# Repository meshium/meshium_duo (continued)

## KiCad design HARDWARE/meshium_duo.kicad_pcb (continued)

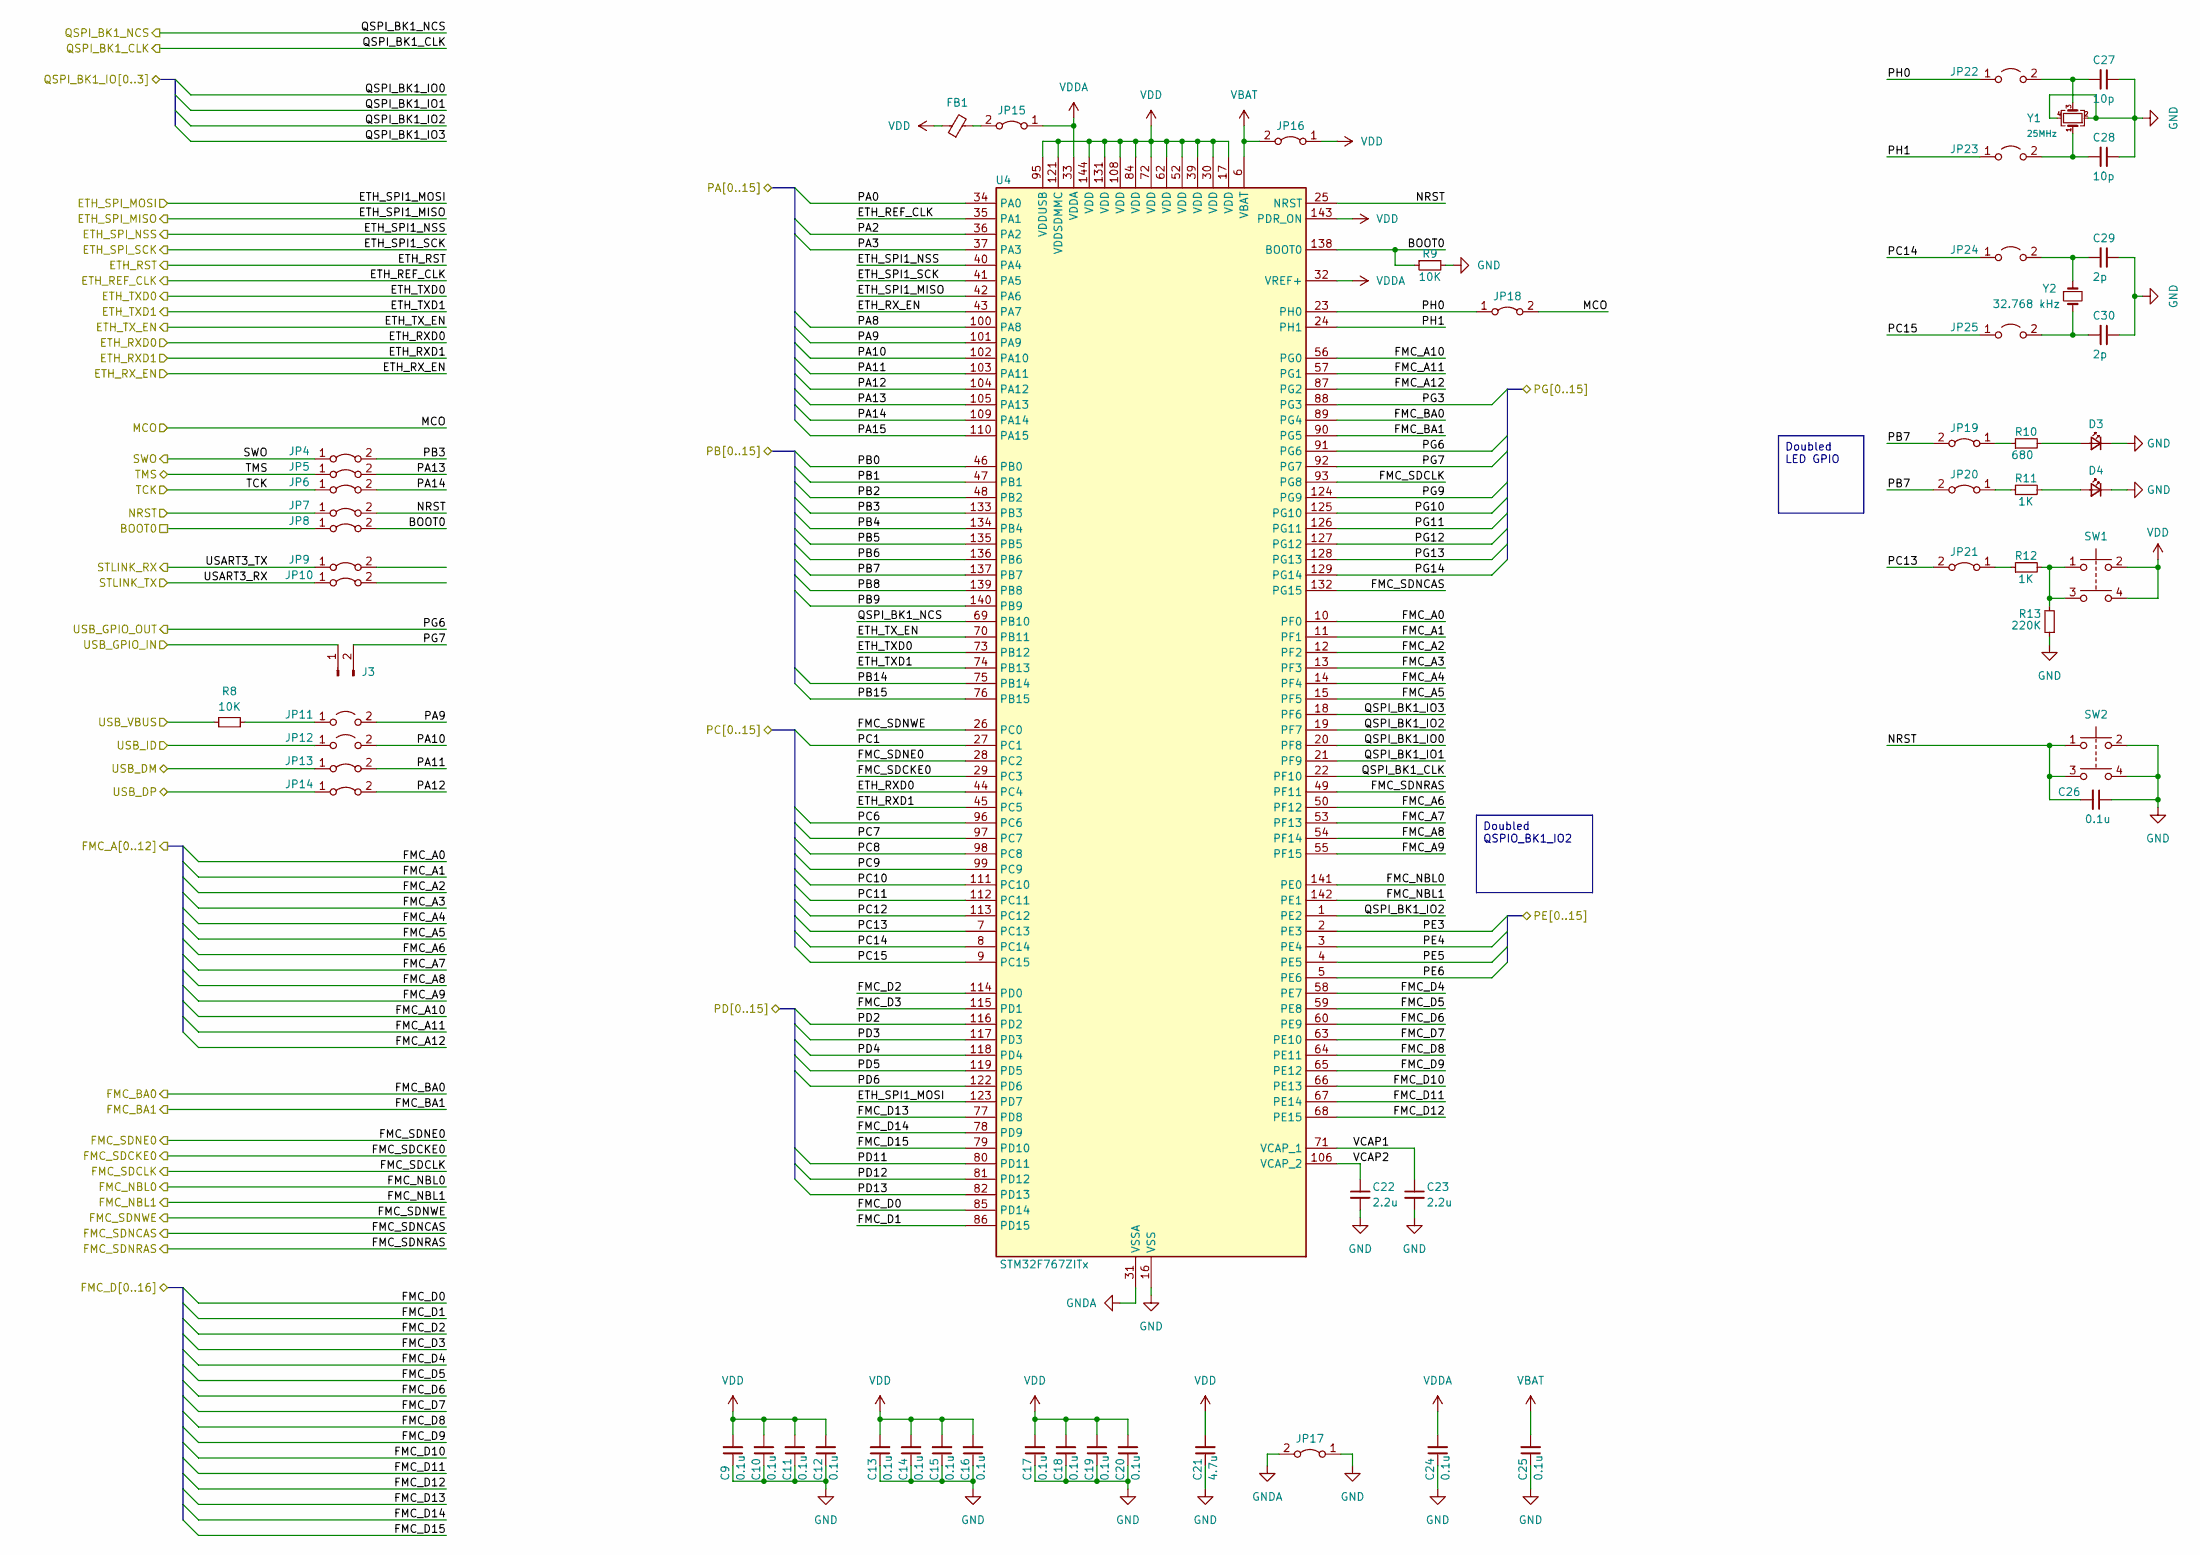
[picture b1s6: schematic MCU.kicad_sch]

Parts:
C9, C10, C11, C12, C13, C14, C15, C16, C17, C18, C19, C20, C24, C25, C26: 0.1u; C_0603_1608Metric
C21: 4.7u; C_0603_1608Metric
C22, C23: 2.2u; C_0805_2012Metric
C27, C28: 10p; C_0603_1608Metric
C29, C30: 2p; C_0603_1608Metric
D3, D4: LED_Small; LED_0603_1608Metric
FB1: FerriteBead_Small; C_0603_1608Metric
J3: Conn_01x02_Pin; PinHeader_1x02_P2.54mm_Vertical
JP4, JP5, JP6, JP7, JP8, JP9, JP10, JP13, JP14, JP15, JP16, JP17, JP18, JP19, JP20, JP21: Jumper_2_Bridged; SolderJumper-2_P1.3mm_Open_TrianglePad1.0x1.5mm
JP11, JP12, JP22, JP23, JP24, JP25: Jumper_2_Open; SolderJumper-2_P1.3mm_Open_TrianglePad1.0x1.5mm
R8, R9: 10K; R_0603_1608Metric
R10: 680; R_0603_1608Metric
R11, R12: 1K; R_0603_1608Metric
R13: 220K; R_0603_1608Metric
SW1, SW2: SW_Push_Dual
U4: STM32F767ZITx; LQFP-144_20x20mm_P0.5mm
Y1: 25MHz; Crystal_SMD_3225-4Pin_3.2x2.5mm
Y2: 32.768 kHz; Crystal_SMD_3215-2Pin_3.2x1.5mm

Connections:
/Connectors/BOOT0: JP8.1 (A), JP8.2 (B), R9.1, U4.138 (BOOT0); also elsewhere on the board
/Connectors/NRST: C26.2, JP7.1 (A), JP7.2 (B), SW2.1, SW2.3, U4.25 (NRST); also elsewhere on the board
/Connectors/PA0: U4.34 (PA0); also elsewhere on the board
/Connectors/PA2: U4.36 (PA2); also elsewhere on the board
/Connectors/PA3: U4.37 (PA3); also elsewhere on the board
/Connectors/PA8: U4.100 (PA8); also elsewhere on the board
/Connectors/PA9: JP11.2 (B), U4.101 (PA9); also elsewhere on the board
/Connectors/PA10: JP12.2 (B), U4.102 (PA10); also elsewhere on the board
/Connectors/PA11: JP13.2 (B), U4.103 (PA11); also elsewhere on the board
/Connectors/PA12: JP14.2 (B), U4.104 (PA12); also elsewhere on the board
/Connectors/PA13: JP5.2 (B), U4.105 (PA13); also elsewhere on the board
/Connectors/PA14: JP6.2 (B), U4.109 (PA14); also elsewhere on the board
/Connectors/PA15: U4.110 (PA15); also elsewhere on the board
/Connectors/PB0: U4.46 (PB0); also elsewhere on the board
/Connectors/PB1: U4.47 (PB1); also elsewhere on the board
/Connectors/PB2: U4.48 (PB2); also elsewhere on the board
/Connectors/PB3: JP4.2 (B), U4.133 (PB3); also elsewhere on the board
/Connectors/PB4: U4.134 (PB4); also elsewhere on the board
/Connectors/PB5: U4.135 (PB5); also elsewhere on the board
/Connectors/PB6: U4.136 (PB6); also elsewhere on the board
/Connectors/PB7: JP19.2 (B), JP20.2 (B), U4.137 (PB7); also elsewhere on the board
/Connectors/PB8: U4.139 (PB8); also elsewhere on the board
/Connectors/PB9: U4.140 (PB9); also elsewhere on the board
/Connectors/PB14: U4.75 (PB14); also elsewhere on the board
/Connectors/PB15: U4.76 (PB15); also elsewhere on the board
/Connectors/PC1: U4.27 (PC1); also elsewhere on the board
/Connectors/PC6: U4.96 (PC6); also elsewhere on the board
/Connectors/PC7: U4.97 (PC7); also elsewhere on the board
/Connectors/PC8: U4.98 (PC8); also elsewhere on the board
/Connectors/PC9: U4.99 (PC9); also elsewhere on the board
/Connectors/PC10: U4.111 (PC10); also elsewhere on the board
/Connectors/PC11: U4.112 (PC11); also elsewhere on the board
/Connectors/PC12: U4.113 (PC12); also elsewhere on the board
/Connectors/PC13: JP21.2 (B), U4.7 (PC13); also elsewhere on the board
/Connectors/PC14: JP24.1 (A), U4.8 (PC14); also elsewhere on the board
/Connectors/PC15: JP25.1 (A), U4.9 (PC15); also elsewhere on the board
/Connectors/PD2: U4.116 (PD2); also elsewhere on the board
/Connectors/PD3: U4.117 (PD3); also elsewhere on the board
/Connectors/PD4: U4.118 (PD4); also elsewhere on the board
/Connectors/PD5: U4.119 (PD5); also elsewhere on the board
/Connectors/PD6: U4.122 (PD6); also elsewhere on the board
/Connectors/PD11: U4.80 (PD11); also elsewhere on the board
/Connectors/PD12: U4.81 (PD12); also elsewhere on the board
/Connectors/PD13: U4.82 (PD13); also elsewhere on the board
/Connectors/PE3: U4.2 (PE3); also elsewhere on the board
/Connectors/PE4: U4.3 (PE4); also elsewhere on the board
/Connectors/PE5: U4.4 (PE5); also elsewhere on the board
/Connectors/PE6: U4.5 (PE6); also elsewhere on the board
/Connectors/PG3: U4.88 (PG3); also elsewhere on the board
/Connectors/PG6: U4.91 (PG6); also elsewhere on the board
/Connectors/PG7: J3.2, U4.92 (PG7); also elsewhere on the board
/Connectors/PG9: U4.124 (PG9); also elsewhere on the board
/Connectors/PG10: U4.125 (PG10); also elsewhere on the board
/Connectors/PG11: U4.126 (PG11); also elsewhere on the board
/Connectors/PG12: U4.127 (PG12); also elsewhere on the board
/Connectors/PG13: U4.128 (PG13); also elsewhere on the board
/Connectors/PG14: U4.129 (PG14); also elsewhere on the board
/Ethernet/ETH_REF_CLK: U4.35 (PA1); also elsewhere on the board
/Ethernet/ETH_RXD0: U4.44 (PC4); also elsewhere on the board
/Ethernet/ETH_RXD1: U4.45 (PC5); also elsewhere on the board
/Ethernet/ETH_RX_EN: U4.43 (PA7); also elsewhere on the board
/Ethernet/ETH_SPI_MISO: U4.42 (PA6); also elsewhere on the board
/Ethernet/ETH_SPI_MOSI: U4.123 (PD7); also elsewhere on the board
/Ethernet/ETH_SPI_NSS: U4.40 (PA4); also elsewhere on the board
/Ethernet/ETH_SPI_SCK: U4.41 (PA5); also elsewhere on the board
/Ethernet/ETH_TXD0: U4.73 (PB12); also elsewhere on the board
/Ethernet/ETH_TXD1: U4.74 (PB13); also elsewhere on the board
/Ethernet/ETH_TX_EN: U4.70 (PB11); also elsewhere on the board
/MCU/FMC_A0: U4.10 (PF0); also elsewhere on the board
/MCU/FMC_A1: U4.11 (PF1); also elsewhere on the board
/MCU/FMC_A2: U4.12 (PF2); also elsewhere on the board
/MCU/FMC_A3: U4.13 (PF3); also elsewhere on the board
/MCU/FMC_A4: U4.14 (PF4); also elsewhere on the board
/MCU/FMC_A5: U4.15 (PF5); also elsewhere on the board
/MCU/FMC_A6: U4.50 (PF12); also elsewhere on the board
/MCU/FMC_A7: U4.53 (PF13); also elsewhere on the board
/MCU/FMC_A8: U4.54 (PF14); also elsewhere on the board
/MCU/FMC_A9: U4.55 (PF15); also elsewhere on the board
/MCU/FMC_A10: U4.56 (PG0); also elsewhere on the board
/MCU/FMC_A11: U4.57 (PG1); also elsewhere on the board
/MCU/FMC_A12: U4.87 (PG2); also elsewhere on the board
/MCU/FMC_BA0: U4.89 (PG4); also elsewhere on the board
/MCU/FMC_BA1: U4.90 (PG5); also elsewhere on the board
/MCU/FMC_D0: U4.85 (PD14); also elsewhere on the board
/MCU/FMC_D1: U4.86 (PD15); also elsewhere on the board
/MCU/FMC_D2: U4.114 (PD0); also elsewhere on the board
/MCU/FMC_D3: U4.115 (PD1); also elsewhere on the board
/MCU/FMC_D4: U4.58 (PE7); also elsewhere on the board
/MCU/FMC_D5: U4.59 (PE8); also elsewhere on the board
/MCU/FMC_D6: U4.60 (PE9); also elsewhere on the board
/MCU/FMC_D7: U4.63 (PE10); also elsewhere on the board
/MCU/FMC_D8: U4.64 (PE11); also elsewhere on the board
/MCU/FMC_D9: U4.65 (PE12); also elsewhere on the board
/MCU/FMC_D10: U4.66 (PE13); also elsewhere on the board
/MCU/FMC_D11: U4.67 (PE14); also elsewhere on the board
/MCU/FMC_D12: U4.68 (PE15); also elsewhere on the board
/MCU/FMC_D13: U4.77 (PD8); also elsewhere on the board
/MCU/FMC_D14: U4.78 (PD9); also elsewhere on the board
/MCU/FMC_D15: U4.79 (PD10); also elsewhere on the board
/MCU/FMC_NBL0: U4.141 (PE0); also elsewhere on the board
/MCU/FMC_NBL1: U4.142 (PE1); also elsewhere on the board
/MCU/FMC_SDCKE0: U4.29 (PC3); also elsewhere on the board
/MCU/FMC_SDCLK: U4.93 (PG8); also elsewhere on the board
/MCU/FMC_SDNCAS: U4.132 (PG15); also elsewhere on the board
/MCU/FMC_SDNE0: U4.28 (PC2); also elsewhere on the board
/MCU/FMC_SDNRAS: U4.49 (PF11); also elsewhere on the board
/MCU/FMC_SDNWE: U4.26 (PC0); also elsewhere on the board
/MCU/MCO: JP18.2 (B); also elsewhere on the board
/MCU/PH0: JP18.1 (A), JP22.1 (A), U4.23 (PH0)
/MCU/PH1: JP23.1 (A), U4.24 (PH1)
/MCU/QSPI_BK1_CLK: U4.22 (PF10); also elsewhere on the board
/MCU/QSPI_BK1_IO0: U4.20 (PF8); also elsewhere on the board
/MCU/QSPI_BK1_IO1: U4.21 (PF9); also elsewhere on the board
/MCU/QSPI_BK1_IO2: U4.1 (PE2), U4.19 (PF7); also elsewhere on the board
/MCU/QSPI_BK1_IO3: U4.18 (PF6); also elsewhere on the board
/MCU/QSPI_BK1_NCS: U4.69 (PB10); also elsewhere on the board
/MCU/SWO: JP4.1 (A); also elsewhere on the board
/MCU/TCK: JP6.1 (A); also elsewhere on the board
/MCU/TMS: JP5.1 (A); also elsewhere on the board
/MCU/USART3_RX: JP10.1 (A); also elsewhere on the board
/MCU/USART3_TX: JP9.1 (A); also elsewhere on the board
/MCU/USB_DM: JP13.1 (A); also elsewhere on the board
/MCU/USB_DP: JP14.1 (A); also elsewhere on the board
/MCU/USB_GPIO_IN: J3.1; also elsewhere on the board
/MCU/USB_ID: JP12.1 (A); also elsewhere on the board
/MCU/USB_VBUS: R8.1; also elsewhere on the board
GNDA: JP17.2 (B), U4.31 (VSSA); also elsewhere on the board
unnamed: D3.2 (A), R10.2
unnamed: D4.2 (A), R11.2
unnamed: JP11.1 (A), R8.2
unnamed: FB1.2, JP15.2 (B)
unnamed: JP19.1 (A), R10.1
unnamed: JP20.1 (A), R11.1
unnamed: JP21.1 (A), R12.1
unnamed: C27.2, JP22.2 (B), Y1.3
unnamed: C28.2, JP23.2 (B), Y1.1
unnamed: C29.2, JP24.2 (B), Y2.1
unnamed: C30.2, JP25.2 (B), Y2.3
unnamed: R12.2, R13.2, SW1.1, SW1.3
unnamed: C23.1, U4.71 (VCAP_1)
unnamed: C22.1, U4.106 (VCAP_2)
VBAT: C25.2, JP16.2 (B), U4.6 (VBAT); also elsewhere on the board
VDD: C9.2, C10.2, C11.2, C12.2, C13.2, C14.2, C15.2, C16.2, C17.2, C18.2, C19.2, C20.2, C21.2, FB1.1, JP16.1 (A), SW1.2, SW1.4, U4.17 (VDD), U4.30 (VDD), U4.39 (VDD), U4.52 (VDD), U4.62 (VDD), U4.72 (VDD), U4.84 (VDD), U4.95 (VDDUSB), U4.108 (VDD), U4.121 (VDDSDMMC), U4.131 (VDD), U4.143 (PDR_ON), U4.144 (VDD); also elsewhere on the board
VDDA: C24.2, JP15.1 (A), U4.32 (VREF+), U4.33 (VDDA); also elsewhere on the board

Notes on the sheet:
Doubled QSPIO_BK1_IO2
Doubled LED GPIO

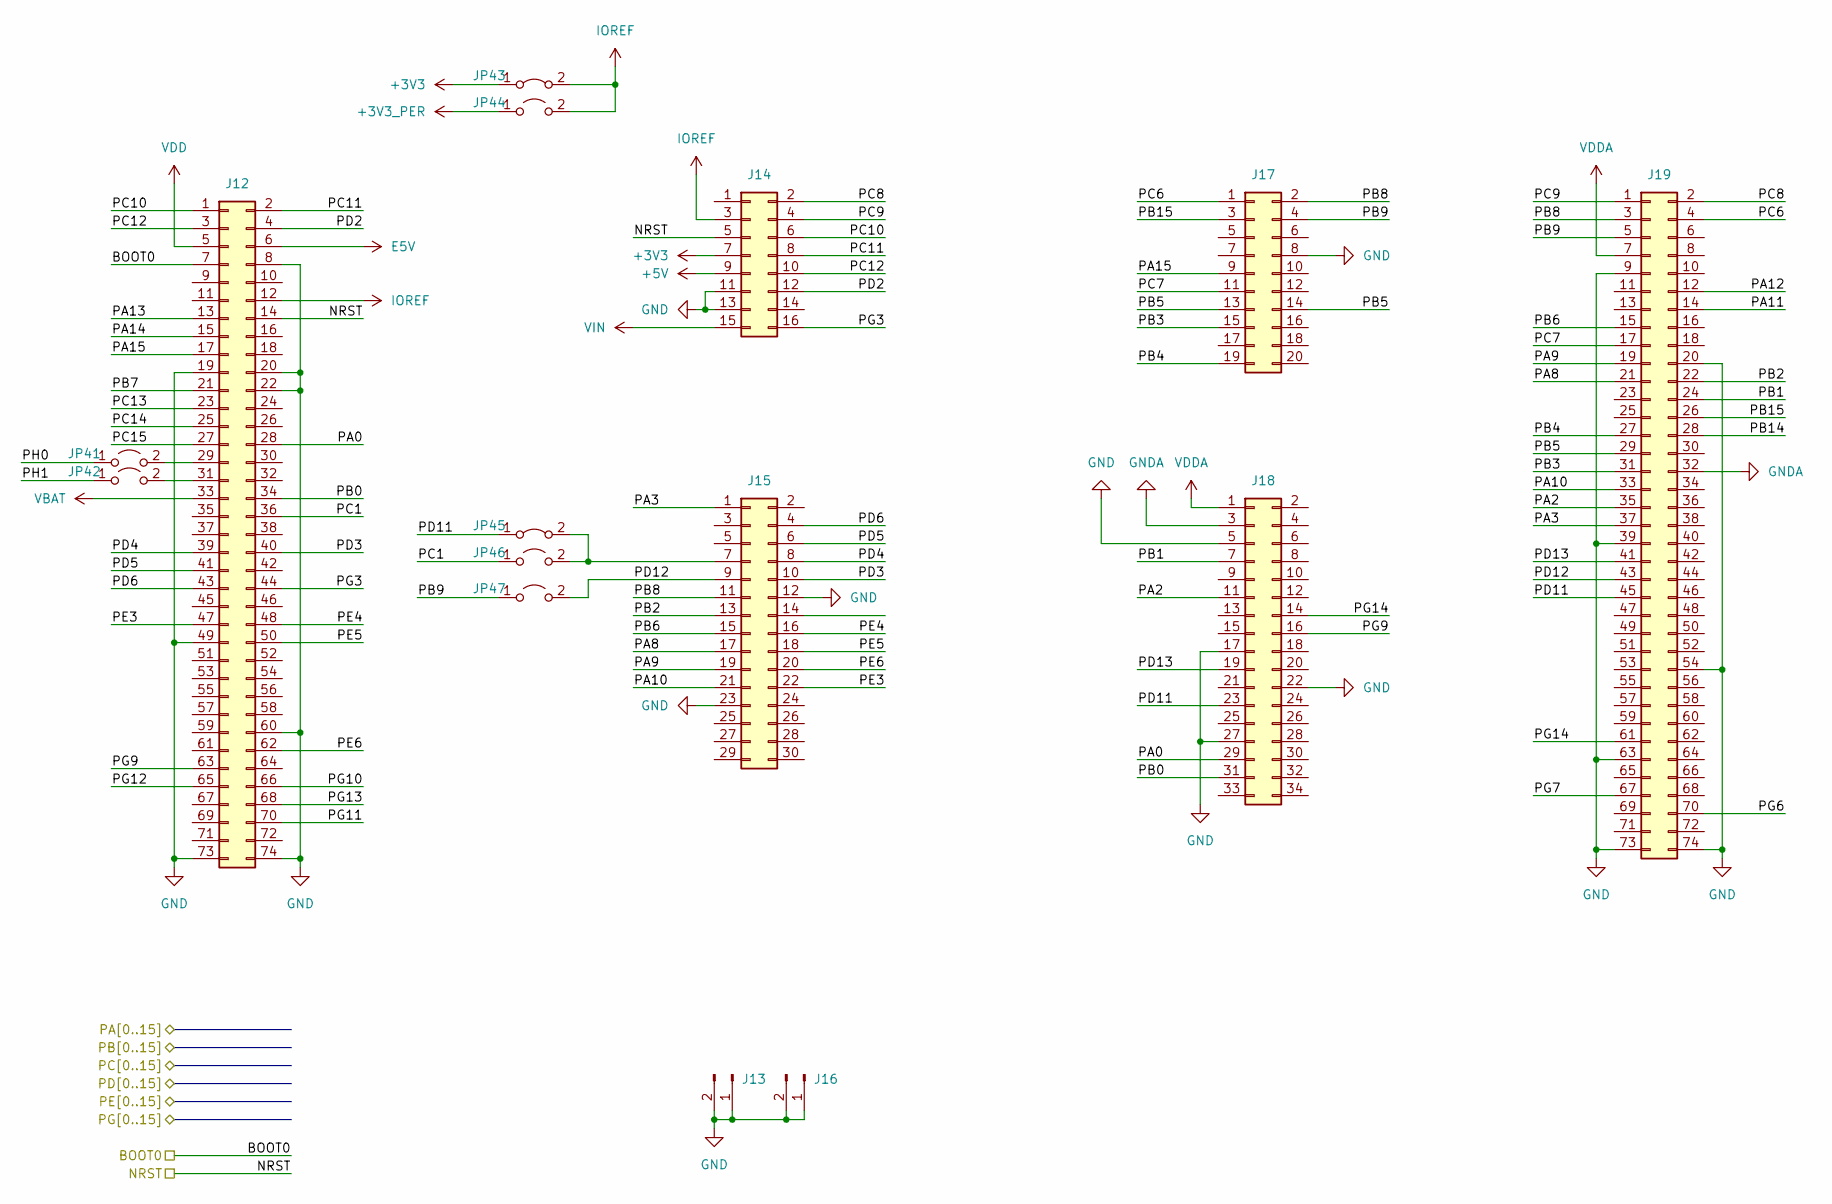
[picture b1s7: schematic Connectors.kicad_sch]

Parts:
J12, J19: Conn_02x37_Odd_Even; PinHeader_2x37_P2.54mm_Vertical
J13, J16: Conn_01x02_Pin; PinHeader_1x02_P2.54mm_Vertical
J14: Conn_02x08_Odd_Even; PinHeader_2x08_P2.54mm_Vertical
J15: Conn_02x15_Odd_Even; PinHeader_2x15_P2.54mm_Vertical
J17: Conn_02x10_Odd_Even; PinHeader_2x10_P2.54mm_Vertical
J18: Conn_02x17_Odd_Even; PinHeader_2x16_P2.54mm_Vertical
JP41, JP42, JP44, JP46, JP47: Jumper_2_Open; SolderJumper-2_P1.3mm_Open_TrianglePad1.0x1.5mm
JP43, JP45: Jumper_2_Bridged; SolderJumper-2_P1.3mm_Open_TrianglePad1.0x1.5mm

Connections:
+3V3_PER: JP44.1 (A); also elsewhere on the board
+5V: J14.9; also elsewhere on the board
/Connectors/BOOT0: J12.7; also elsewhere on the board
/Connectors/NRST: J12.14, J14.5; also elsewhere on the board
/Connectors/PA0: J12.28, J18.29; also elsewhere on the board
/Connectors/PA2: J18.11, J19.35; also elsewhere on the board
/Connectors/PA3: J15.1, J19.37; also elsewhere on the board
/Connectors/PA8: J15.17, J19.21; also elsewhere on the board
/Connectors/PA9: J15.19, J19.19; also elsewhere on the board
/Connectors/PA10: J15.21, J19.33; also elsewhere on the board
/Connectors/PA11: J19.14; also elsewhere on the board
/Connectors/PA12: J19.12; also elsewhere on the board
/Connectors/PA13: J12.13; also elsewhere on the board
/Connectors/PA14: J12.15; also elsewhere on the board
/Connectors/PA15: J12.17, J17.9; also elsewhere on the board
/Connectors/PB0: J12.34, J18.31; also elsewhere on the board
/Connectors/PB1: J18.7, J19.24; also elsewhere on the board
/Connectors/PB2: J15.13, J19.22; also elsewhere on the board
/Connectors/PB3: J17.15, J19.31; also elsewhere on the board
/Connectors/PB4: J17.19, J19.27; also elsewhere on the board
/Connectors/PB5: J17.13, J17.14, J19.29; also elsewhere on the board
/Connectors/PB6: J15.15, J19.15; also elsewhere on the board
/Connectors/PB7: J12.21; also elsewhere on the board
/Connectors/PB8: J15.11, J17.2, J19.3; also elsewhere on the board
/Connectors/PB9: J17.4, J19.5, JP47.1 (A); also elsewhere on the board
/Connectors/PB14: J19.28; also elsewhere on the board
/Connectors/PB15: J17.3, J19.26; also elsewhere on the board
/Connectors/PC1: J12.36, JP46.1 (A); also elsewhere on the board
/Connectors/PC6: J17.1, J19.4; also elsewhere on the board
/Connectors/PC7: J17.11, J19.17; also elsewhere on the board
/Connectors/PC8: J14.2, J19.2; also elsewhere on the board
/Connectors/PC9: J14.4, J19.1; also elsewhere on the board
/Connectors/PC10: J12.1, J14.6; also elsewhere on the board
/Connectors/PC11: J12.2, J14.8; also elsewhere on the board
/Connectors/PC12: J12.3, J14.10; also elsewhere on the board
/Connectors/PC13: J12.23; also elsewhere on the board
/Connectors/PC14: J12.25; also elsewhere on the board
/Connectors/PC15: J12.27; also elsewhere on the board
/Connectors/PD2: J12.4, J14.12; also elsewhere on the board
/Connectors/PD3: J12.40, J15.10; also elsewhere on the board
/Connectors/PD4: J12.39, J15.8; also elsewhere on the board
/Connectors/PD5: J12.41, J15.6; also elsewhere on the board
/Connectors/PD6: J12.43, J15.4; also elsewhere on the board
/Connectors/PD11: J18.23, J19.45, JP45.1 (A); also elsewhere on the board
/Connectors/PD12: J15.9, J19.43, JP47.2 (B); also elsewhere on the board
/Connectors/PD13: J18.19, J19.41; also elsewhere on the board
/Connectors/PE3: J12.47, J15.22; also elsewhere on the board
/Connectors/PE4: J12.48, J15.16; also elsewhere on the board
/Connectors/PE5: J12.50, J15.18; also elsewhere on the board
/Connectors/PE6: J12.62, J15.20; also elsewhere on the board
/Connectors/PG3: J12.44, J14.16; also elsewhere on the board
/Connectors/PG6: J19.70; also elsewhere on the board
/Connectors/PG7: J19.67; also elsewhere on the board
/Connectors/PG9: J12.63, J18.16; also elsewhere on the board
/Connectors/PG10: J12.66; also elsewhere on the board
/Connectors/PG11: J12.70; also elsewhere on the board
/Connectors/PG12: J12.65; also elsewhere on the board
/Connectors/PG13: J12.68; also elsewhere on the board
/Connectors/PG14: J18.14, J19.61; also elsewhere on the board
/Connectors/PH0: JP41.1 (A)
/Connectors/PH1: JP42.1 (A)
E5V: J12.6; also elsewhere on the board
GNDA: J18.3, J19.32; also elsewhere on the board
IOREF: J12.12, J14.3, JP43.2 (B), JP44.2 (B)
unnamed: J12.29, JP41.2 (B)
unnamed: J12.31, JP42.2 (B)
unnamed: J15.7, JP45.2 (B), JP46.2 (B)
VBAT: J12.33; also elsewhere on the board
VDD: J12.5; also elsewhere on the board
VDDA: J18.1, J19.7; also elsewhere on the board
VIN: J14.15; also elsewhere on the board

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
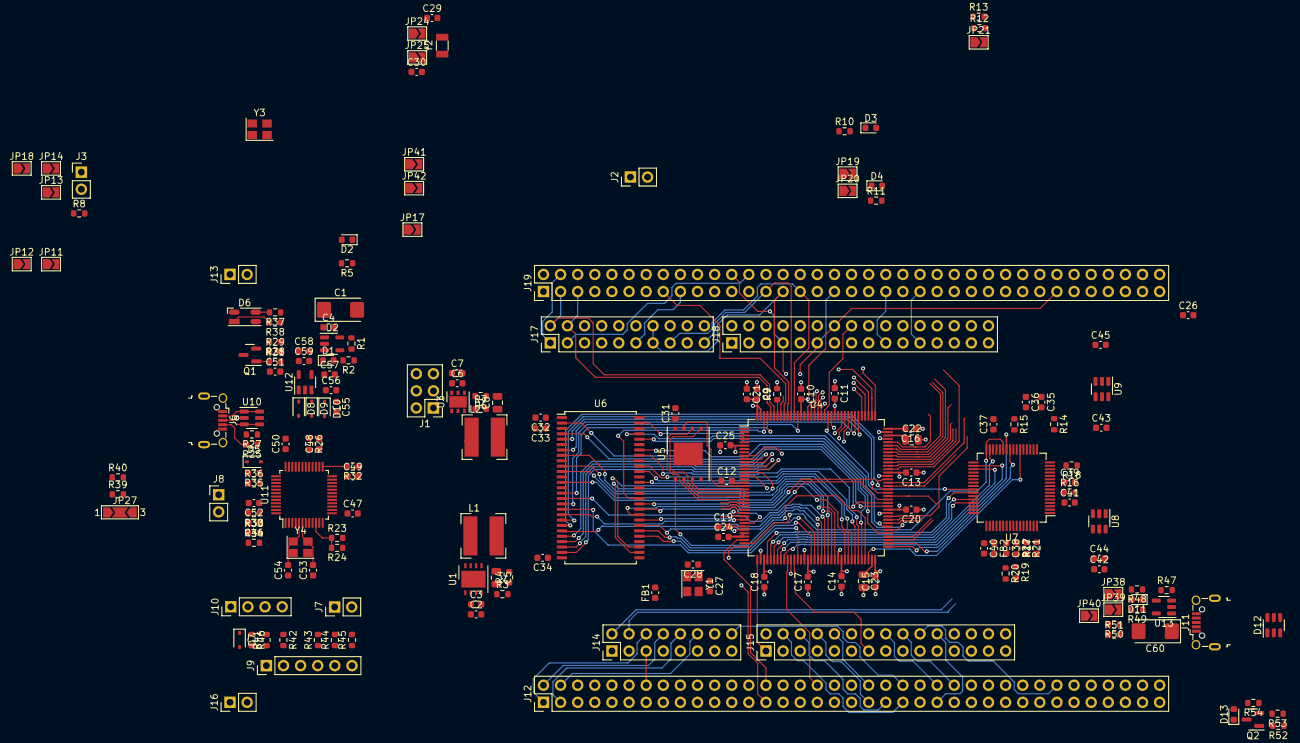
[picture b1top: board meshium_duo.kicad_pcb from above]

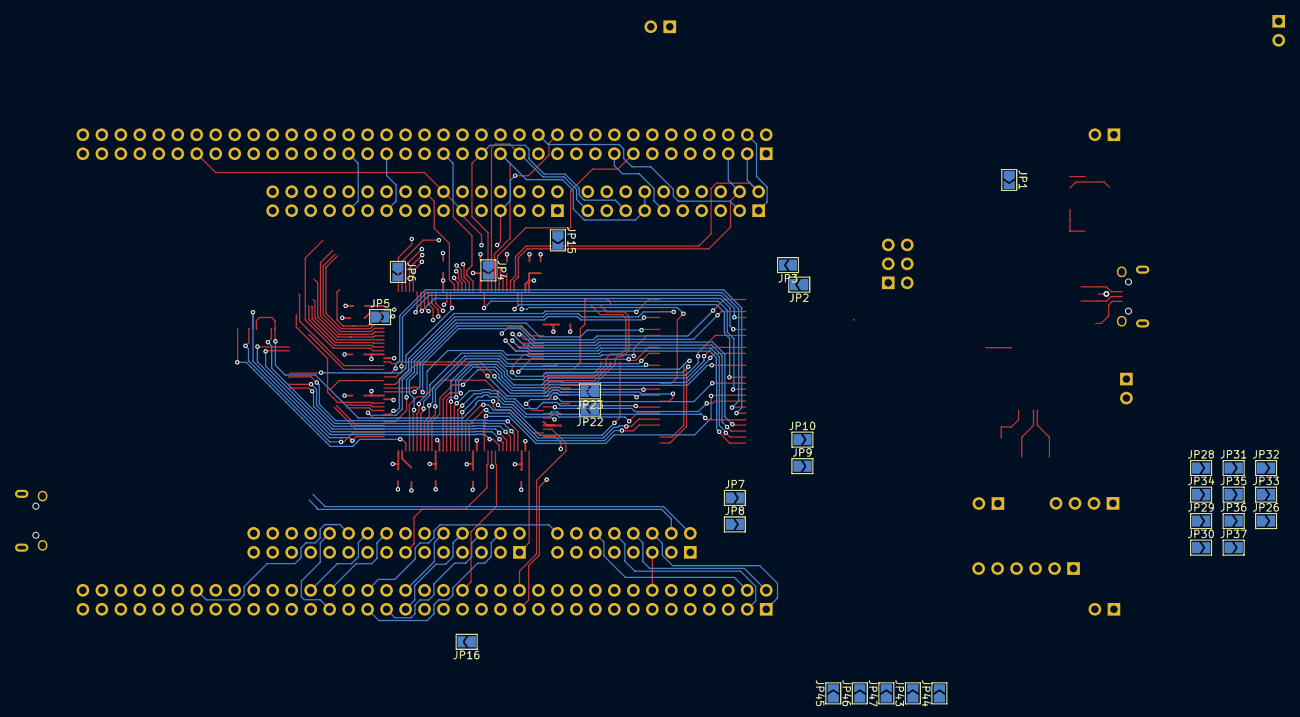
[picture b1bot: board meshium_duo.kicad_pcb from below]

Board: 6 copper layers, 214 parts (30 on the bottom side), 235 nets.

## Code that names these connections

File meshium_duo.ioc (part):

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Mcu.Name=STM32F767ZGTx
Mcu.Package=LQFP144
Mcu.UserName=STM32F767ZGTx
PA1.Mode=RMII
PA1.Signal=ETH_REF_CLK
PA2.Mode=RMII
PA2.Signal=ETH_MDIO
PA4.Mode=NSS_Signal_Hard_Output
PA4.Signal=SPI1_NSS
PA5.Mode=Full_Duplex_Master
PA5.Signal=SPI1_SCK
PA6.Mode=Full_Duplex_Master
PA6.Signal=SPI1_MISO
PA7.Mode=RMII
PA7.Signal=ETH_CRS_DV
PB10.Mode=Single Bank 1
PB10.Signal=QUADSPI_BK1_NCS
PB11.Mode=RMII
PB11.Signal=ETH_TX_EN
PB12.Mode=RMII
PB12.Signal=ETH_TXD0
PB13.Mode=RMII
PB13.Signal=ETH_TXD1
PC0.Signal=FMC_SDNWE
PC1.Mode=RMII
PC1.Signal=ETH_MDC
PC10.Mode=SD_4_bits_Wide_bus
PC10.Signal=SDMMC1_D2
PC11.Mode=SD_4_bits_Wide_bus
PC11.Signal=SDMMC1_D3
PC12.Mode=SD_4_bits_Wide_bus
PC12.Signal=SDMMC1_CK
PC2.Mode=SdramChipSelect1_1
PC2.Signal=FMC_SDNE0
PC3.Mode=SdramChipSelect1_1
PC3.Signal=FMC_SDCKE0
PC4.Mode=RMII
PC4.Signal=ETH_RXD0
PC5.Mode=RMII
PC5.Signal=ETH_RXD1
PC8.Mode=SD_4_bits_Wide_bus
PC8.Signal=SDMMC1_D0
PC9.Mode=SD_4_bits_Wide_bus
PC9.Signal=SDMMC1_D1
PD0.Signal=FMC_D2_DA2
PD1.Signal=FMC_D3_DA3
PD10.Signal=FMC_D15_DA15
PD14.Signal=FMC_D0_DA0
PD15.Signal=FMC_D1_DA1
PD2.Mode=SD_4_bits_Wide_bus
PD2.Signal=SDMMC1_CMD
PD7.Mode=Full_Duplex_Master
PD7.Signal=SPI1_MOSI
PD8.Signal=FMC_D13_DA13
PD9.Signal=FMC_D14_DA14
PE0.Signal=FMC_NBL0
PE1.Signal=FMC_NBL1
PE10.Signal=FMC_D7_DA7
PE11.Signal=FMC_D8_DA8
PE12.Signal=FMC_D9_DA9
PE13.Signal=FMC_D10_DA10
PE14.Signal=FMC_D11_DA11
PE15.Signal=FMC_D12_DA12
PE2.Mode=Single Bank 1
PE2.Signal=QUADSPI_BK1_IO2
PE7.Signal=FMC_D4_DA4
PE8.Signal=FMC_D5_DA5
PE9.Signal=FMC_D6_DA6
PF0.Signal=FMC_A0
PF1.Signal=FMC_A1
PF10.Mode=Single Bank 1
PF10.Signal=QUADSPI_CLK
PF11.Signal=FMC_SDNRAS
PF12.Signal=FMC_A6
PF13.Signal=FMC_A7
PF14.Signal=FMC_A8
PF15.Signal=FMC_A9
PF2.Signal=FMC_A2
PF3.Signal=FMC_A3
PF4.Signal=FMC_A4
PF5.Signal=FMC_A5
PF6.Mode=Single Bank 1
PF6.Signal=QUADSPI_BK1_IO3
PF8.Mode=Single Bank 1
PF8.Signal=QUADSPI_BK1_IO0
PF9.Mode=Single Bank 1
PF9.Signal=QUADSPI_BK1_IO1
PG0.Signal=FMC_A10
PG1.Signal=FMC_A11
PG15.Signal=FMC_SDNCAS
PG2.Signal=FMC_A12
PG4.Signal=FMC_A14_BA0
PG5.Signal=FMC_A15_BA1
PG8.Signal=FMC_SDCLK
PH0/OSC_IN.Mode=HSE-External-Oscillator
PH0/OSC_IN.Signal=RCC_OSC_IN
PH1/OSC_OUT.Mode=HSE-External-Oscillator
PH1/OSC_OUT.Signal=RCC_OSC_OUT
RCC.HSE_VALUE=25000000
RCC.SYSCLKFreq_VALUE=200000000
RCC.SYSCLKSource=RCC_SYSCLKSOURCE_PLLCLK
board=custom

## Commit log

2023-10-22 update gitignore
2023-10-22 pcb creation
2023-10-23 schematic capture
2023-11-19 tracerouting
